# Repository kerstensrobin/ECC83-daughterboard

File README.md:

# ECC83-daughterboard

A compact KiCAD module that allows low voltage designs to utilize ECC83/12AX7 valves.

## Contents

- `ECC83-daughterboard/` — KiCAD project files (schematic, PCB layout)
- `ECC83-daughterboard/w_vacuum.pretty/` — 9-pin noval socket footprints (GZC9-B)
- `ECC83-daughterboard/3dmodels/` — 3D STEP model for the S9CPC/VTB9-PT socket and generator script

## Socket

The board uses a **Belton VTB9-PT (S9CPC)** PCB-mount 9-pin noval socket, compatible with the ECC83/12AX7 B9A pinout. The custom STEP model can be regenerated by running `3dmodels/make_s9cpc_step.py` (requires [CadQuery](https://cadquery.readthedocs.io/)).

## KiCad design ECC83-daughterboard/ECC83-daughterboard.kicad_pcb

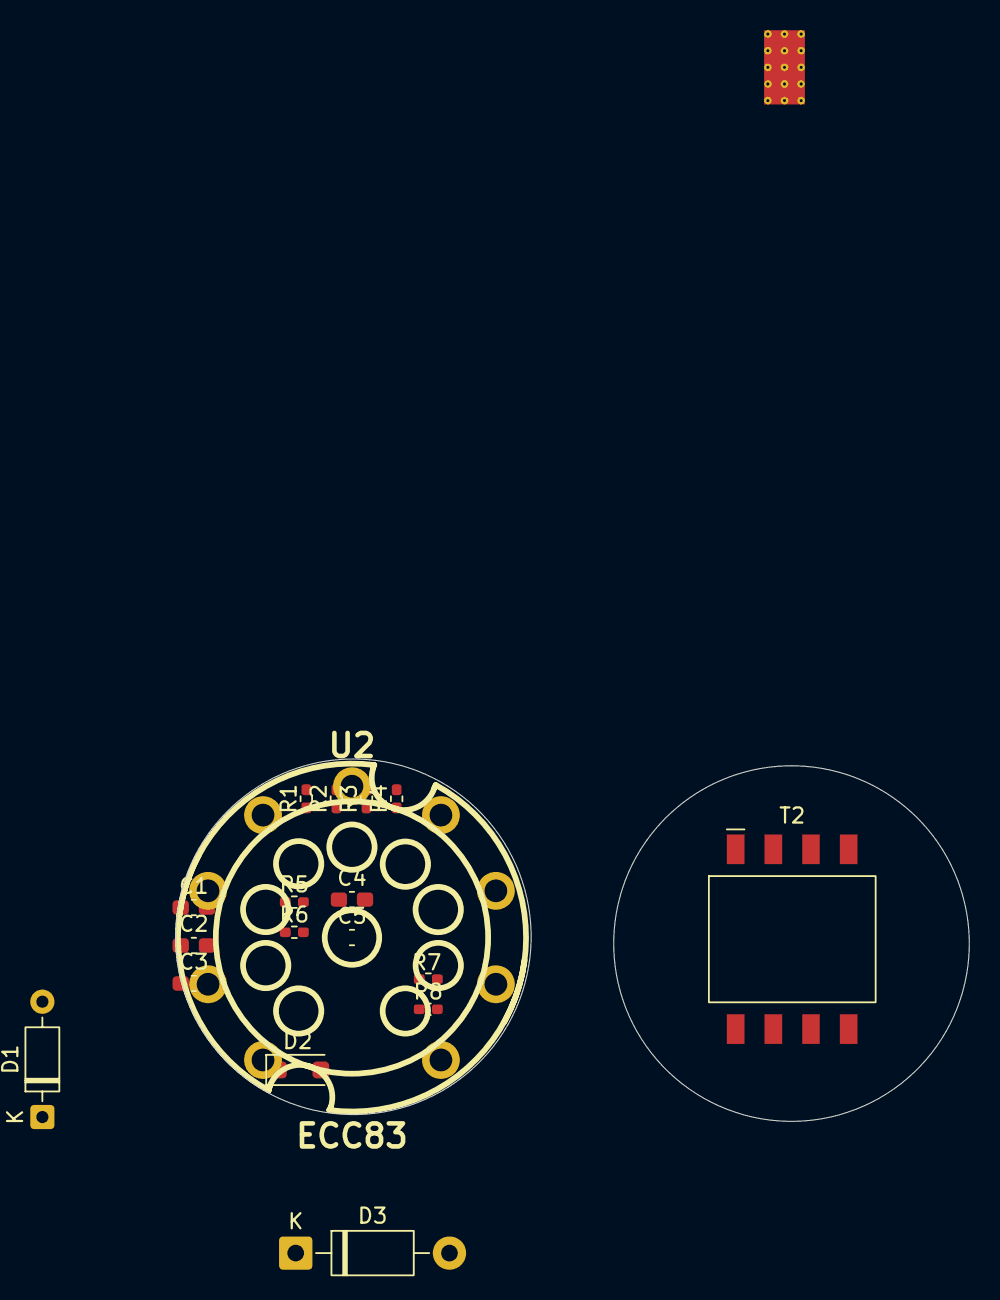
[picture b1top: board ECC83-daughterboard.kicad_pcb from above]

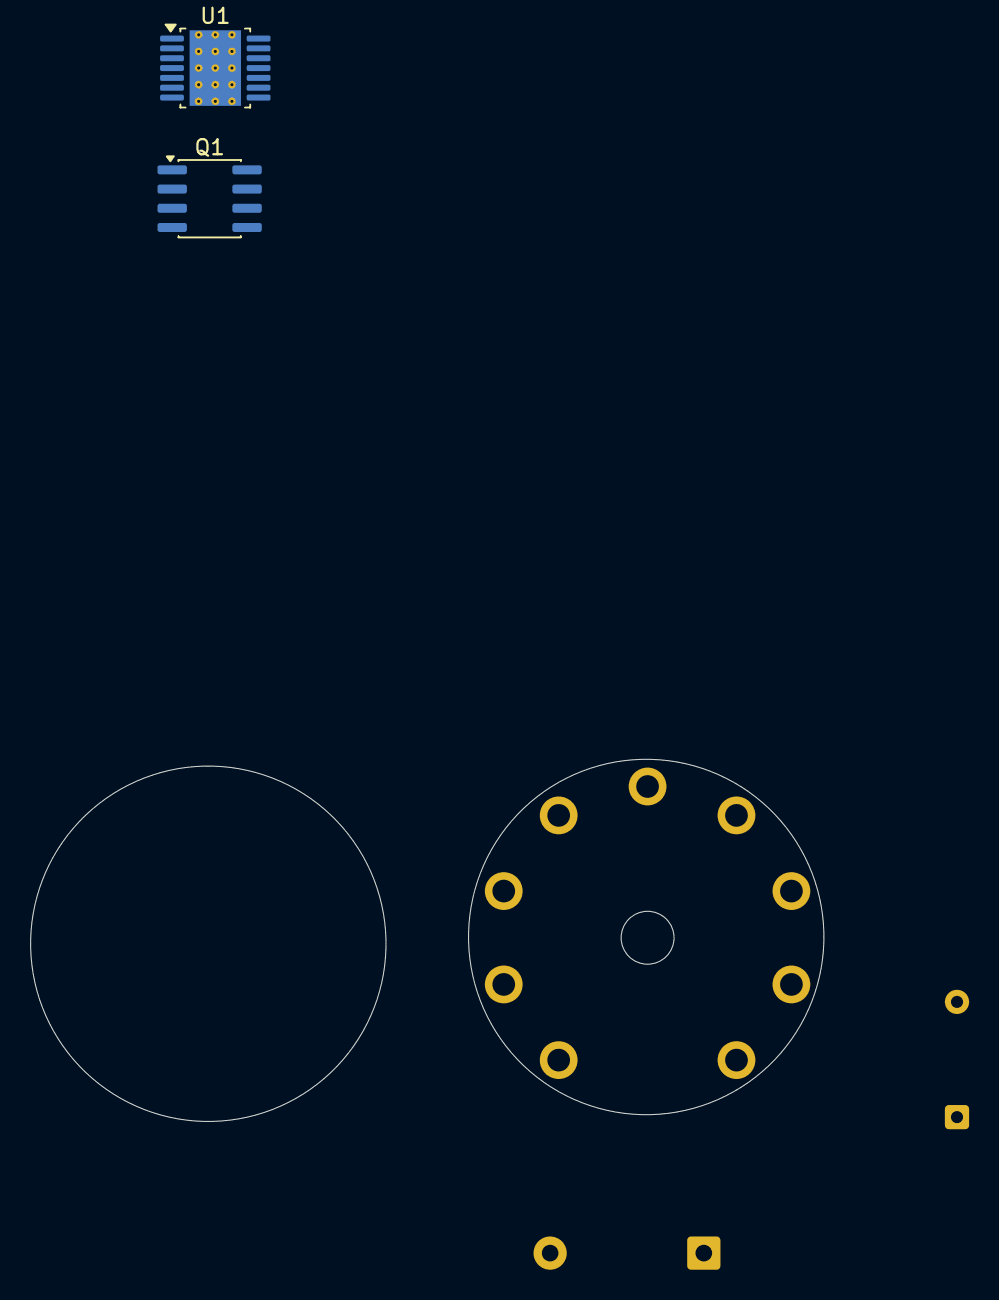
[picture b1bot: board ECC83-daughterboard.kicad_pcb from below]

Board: 2 copper layers, 52.4 x 23.9 mm, 20 parts (2 on the bottom side), 4 nets, no tracks yet.

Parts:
C1, C2, C3, C4, C5: C; C_0603_1608Metric_Pad1.08x0.95mm_HandSolder
D1: BAV21; D_DO-35_SOD27_P7.62mm_Horizontal
D2: BZT52C6V2; D_SOD-123F
D3: MUR160; D_DO-41_SOD81_P10.16mm_Horizontal
Q1: IRF7495; SOIC-8_3.9x4.9mm_P1.27mm
R1, R2, R3, R4, R5, R6, R7, R8: R; R_0402_1005Metric_Pad0.72x0.64mm_HandSolder
T2: EP7_750310020; T_Wurth_WE-PoE-EP7
U1: LM5156HPWP; Texas_HTSSOP-14-1EP_4.4x5mm_P0.65mm_EP3.4x5mm_Mask3.155x3.2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
U2: ECC83; tube_gzc9-b

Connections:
unnamed: Q1.5 (D), Q1.6 (D), Q1.7 (D), Q1.8 (D)
unnamed: Q1.1 (S), Q1.2 (S), Q1.3 (S)
unnamed: R6.1, R7.2
unnamed: U1.6 (AGND), U1.15 (AGND)

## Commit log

2026-04-17 Add S9CPC noval socket 3D model, footprints, and generator script
    - S9CPC_VTB9PT.step: CadQuery-generated STEP model for Belton VTB9-PT
    9-pin noval PCB socket (cream body, gold female contacts, 20mm pin PCD)
    - w_vacuum.pretty: socket_gzc9-b and related footprints from kicad-gigalib
    - make_s9cpc_step.py: script to regenerate/tweak the STEP model
2026-04-17 first files and ecc83 socket step-file
2026-04-17 Remove KiCad_WE-PoE external library, add to .gitignore
2026-04-17 Move S9CPC 3D model and generator script into 3dmodels folder
2026-04-17 Add attribution for w_vacuum footprints from kicad-gigalib by metacollin
2026-04-17 Expand README with project structure and socket details
2026-04-17 moved stuff to correct schematics, decided on a HV controller
2026-04-17 added some design notes for future self
2026-04-20 HV boost schematic in line with datasheet, half-calculated values
